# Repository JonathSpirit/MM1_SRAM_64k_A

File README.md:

# MM1_SRAM_64k_A

Copyright (C) 2020 Guillaume Guillet\
Licensed under CERN-OHL-W v2 or later

<table border="0px">
<tr>
<td>
This source describes Open Hardware and is licensed under the CERN-OHL-W v2 or later.
</td>
</tr>
<tr>
<td>
You may redistribute and modify this documentation and make products
using it under the terms of the CERN-OHL-W v2 (https:/cern.ch/cern-ohl).
This documentation is distributed WITHOUT ANY EXPRESS OR IMPLIED
WARRANTY, INCLUDING OF MERCHANTABILITY, SATISFACTORY QUALITY
AND FITNESS FOR A PARTICULAR PURPOSE. Please see the CERN-OHL-W v2
for applicable conditions.
</td>
</tr>
</table>

Made with [Kicad](https://kicad.org/)

## Description
A SRAM card with 64kBytes of capacity and compatible with [MM1 standard](https://github.com/JonathSpirit/GComputer_standard).

## Status

Version :
> MM1_SRAM_64k_A revision 1

Status :
> Not tested !

Known issues :
> (Empty)

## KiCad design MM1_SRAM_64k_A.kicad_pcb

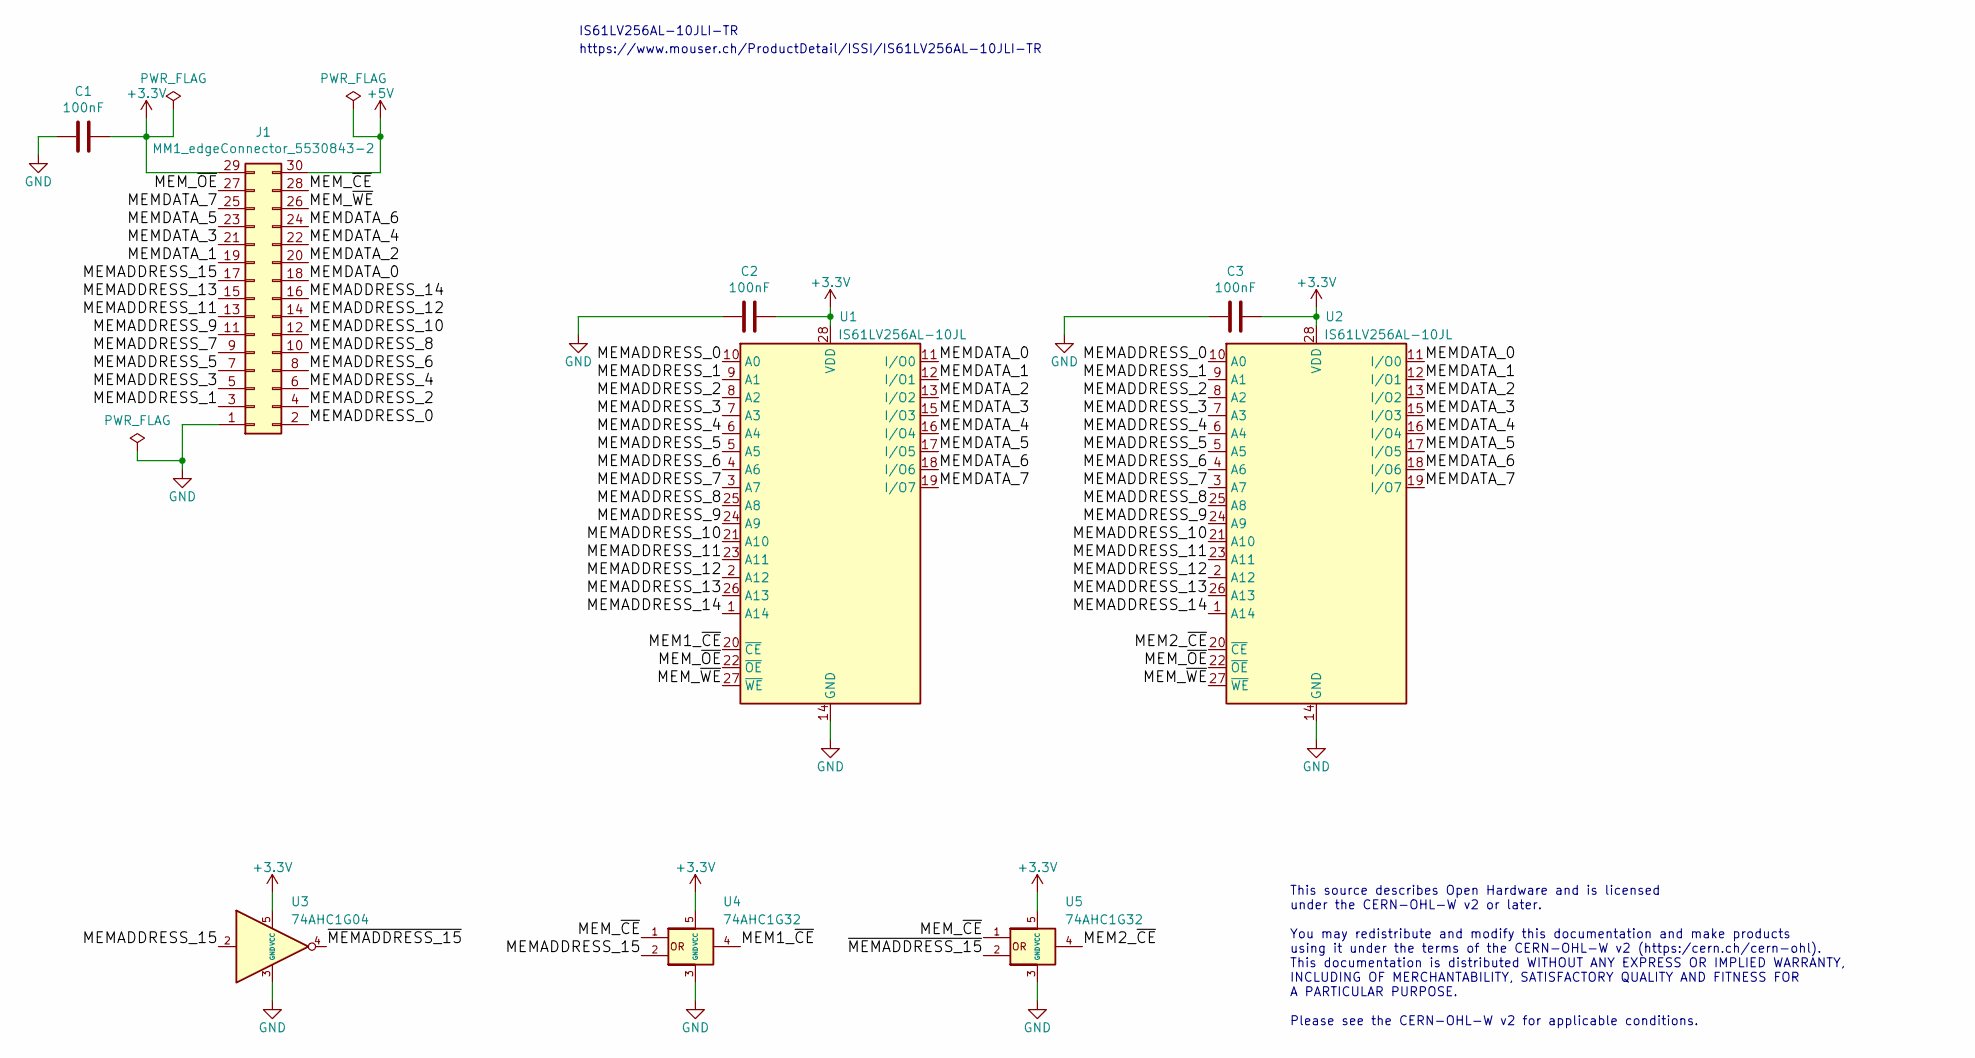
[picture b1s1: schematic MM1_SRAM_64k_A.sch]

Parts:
C1, C2, C3: 100nF; C_0805_2012Metric
J1: MM1_edgeConnector_5530843-2; 5530843-2_edge
U1, U2: IS61LV256AL-10JL; SOJ-28_P1.27mm
U3: 74AHC1G04; SOT-23-5
U4, U5: 74AHC1G32; SOT-23-5

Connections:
+3V3: C1.2, C2.1, C3.1, J1.29, U1.28 (VDD), U2.28 (VDD), U3.5 (VCC), U4.5 (VCC), U5.5 (VCC)
+5V: J1.30
/MEM1_~CE: U1.20 (~CE), U4.4
/MEM2_~CE: U2.20 (~CE), U5.4
/MEMADDRESS_0: J1.2, U1.10 (A0), U2.10 (A0)
/MEMADDRESS_1: J1.3, U1.9 (A1), U2.9 (A1)
/MEMADDRESS_2: J1.4, U1.8 (A2), U2.8 (A2)
/MEMADDRESS_3: J1.5, U1.7 (A3), U2.7 (A3)
/MEMADDRESS_4: J1.6, U1.6 (A4), U2.6 (A4)
/MEMADDRESS_5: J1.7, U1.5 (A5), U2.5 (A5)
/MEMADDRESS_6: J1.8, U1.4 (A6), U2.4 (A6)
/MEMADDRESS_7: J1.9, U1.3 (A7), U2.3 (A7)
/MEMADDRESS_8: J1.10, U1.25 (A8), U2.25 (A8)
/MEMADDRESS_9: J1.11, U1.24 (A9), U2.24 (A9)
/MEMADDRESS_10: J1.12, U1.21 (A10), U2.21 (A10)
/MEMADDRESS_11: J1.13, U1.23 (A11), U2.23 (A11)
/MEMADDRESS_12: J1.14, U1.2 (A12), U2.2 (A12)
/MEMADDRESS_13: J1.15, U1.26 (A13), U2.26 (A13)
/MEMADDRESS_14: J1.16, U1.1 (A14), U2.1 (A14)
/MEMADDRESS_15: J1.17, U3.2, U4.2
/MEMDATA_0: J1.18, U1.11 (I/O0), U2.11 (I/O0)
/MEMDATA_1: J1.19, U1.12 (I/O1), U2.12 (I/O1)
/MEMDATA_2: J1.20, U1.13 (I/O2), U2.13 (I/O2)
/MEMDATA_3: J1.21, U1.15 (I/O3), U2.15 (I/O3)
/MEMDATA_4: J1.22, U1.16 (I/O4), U2.16 (I/O4)
/MEMDATA_5: J1.23, U1.17 (I/O5), U2.17 (I/O5)
/MEMDATA_6: J1.24, U1.18 (I/O6), U2.18 (I/O6)
/MEMDATA_7: J1.25, U1.19 (I/O7), U2.19 (I/O7)
/MEM_~CE: J1.28, U4.1, U5.1
/MEM_~OE: J1.27, U1.22 (~OE), U2.22 (~OE)
/MEM_~WE: J1.26, U1.27 (~WE), U2.27 (~WE)
/~MEMADDRESS_15: U3.4, U5.2
GND: C1.1, C2.2, C3.2, J1.1, U1.14 (GND), U2.14 (GND), U3.3 (GND), U4.3 (GND), U5.3 (GND)

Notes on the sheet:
IS61LV256AL-10JLI-TR
https://www.mouser.ch/ProductDetail/ISSI/IS61LV256AL-10JLI-TR
This source describes Open Hardware and is licensed under the CERN-OHL-W v2 or later. You may redistribute and modify this documentation and make products using it under the terms of the CERN-OHL-W v2 (https:/cern.ch/cern-ohl). This documentation is distributed WITHOUT ANY EXPRESS OR IMPLIED WARRAN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

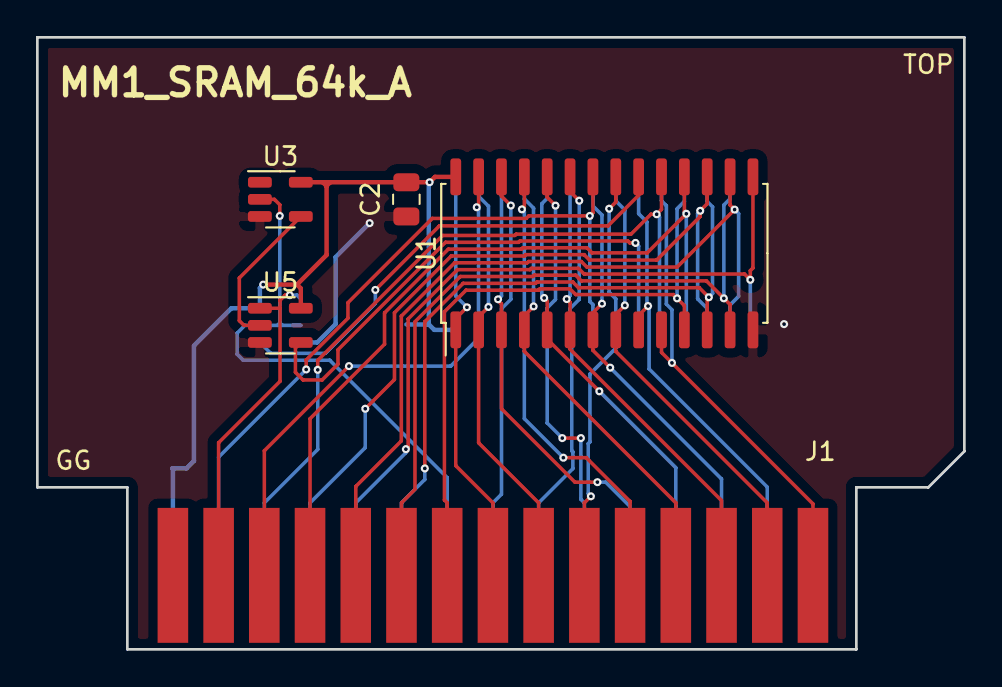
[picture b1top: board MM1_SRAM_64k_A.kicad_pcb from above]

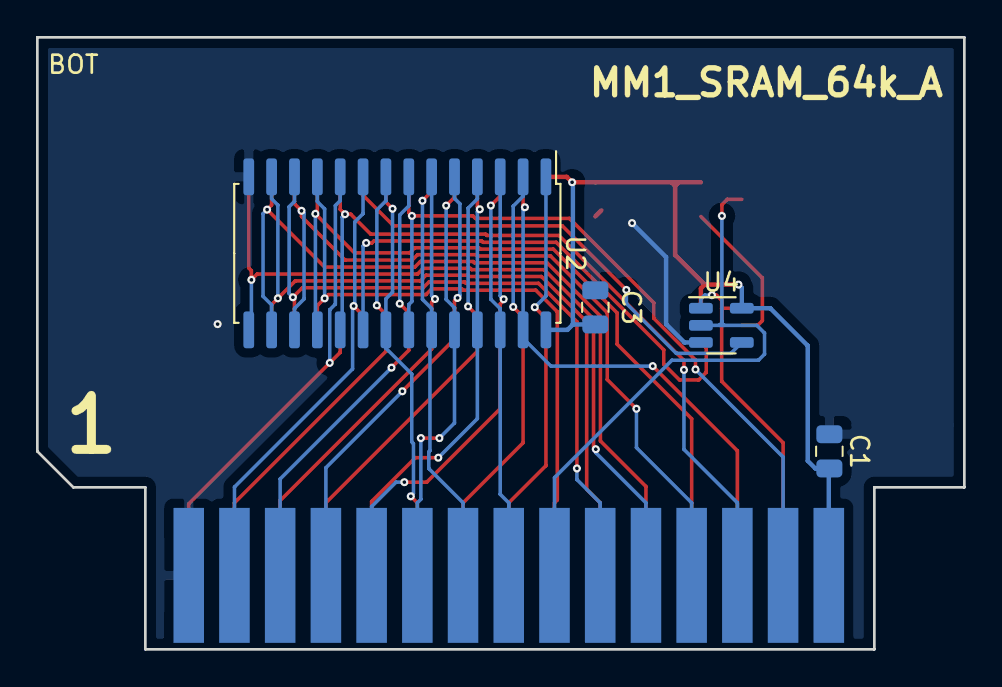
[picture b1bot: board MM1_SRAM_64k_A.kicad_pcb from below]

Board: 2 copper layers, 51.5 x 34.0 mm, 9 parts (4 on the bottom side), 32 nets.

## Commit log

2020-11-20 .gitignore file
2020-11-20 initial push
2020-11-20 add funding file
2020-11-23 custom SOJ-28 footprint and gerbert file
2021-11-08 Update README.md
    https://forum.kicad.info/t/warning-avoid-all-links-to-kicad-pcb-org-use-kicad-org/31521

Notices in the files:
MM1_SRAM_64k_A.kicad_pcb:
Copyright Guillaume Guillet 2020
